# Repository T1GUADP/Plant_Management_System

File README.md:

# Plant_Management_System
This is a project created by: team 1; Real Time Embedded Programming; Glasgow University

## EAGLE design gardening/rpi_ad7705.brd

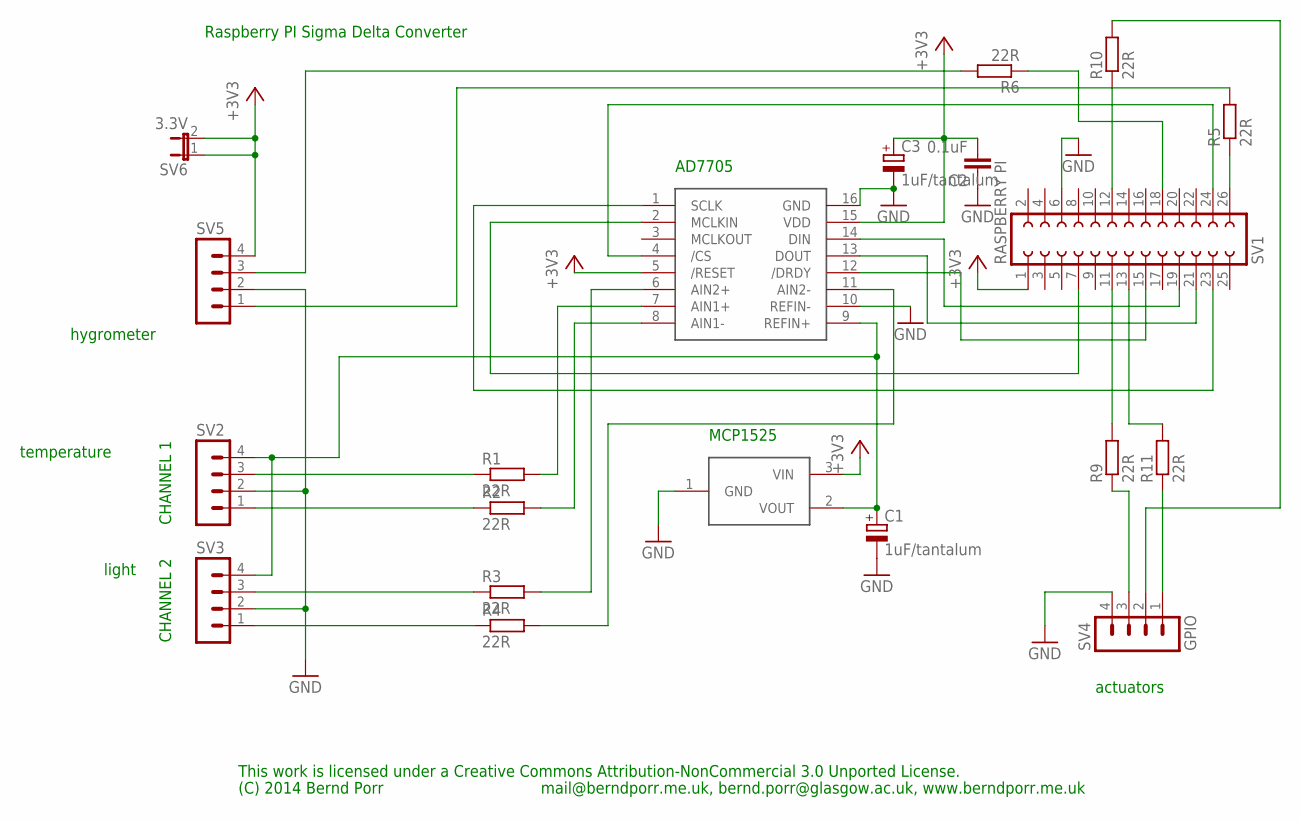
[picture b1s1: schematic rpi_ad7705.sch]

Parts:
C1, C3: 1uF/tantalum; TT2D7
C2: 0.1uF; C5B2.5
R1, R2, R3, R4, R5, R6, R9, R10, R11: 22R; 0207/10
SV1: RASPBERRY PI; FE13-2
SV2, SV3, SV5: MA04-1
SV4: GPIO; MA04-1
SV6: 3.3V; JP1
U$1: AD7705; DIP16
U$2: MCP1525; TO92

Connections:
+3V3: C2.2, C3.+, SV1.1, SV5.4, SV6.1, SV6.2, U$1.5 (/RESET), U$1.15 (VDD), U$2.3 (VIN)
GND: C1.-, C2.1, C3.-, SV1.6, SV2.2, SV3.2, SV4.4, SV5.2, U$1.10 (REFIN-), U$1.16 (GND), U$2.1 (GND)
unnamed: SV1.19, U$1.14 (DIN)
unnamed: SV1.23, U$1.1 (SCLK)
unnamed: SV1.7, U$1.2 (MCLKIN)
unnamed: SV1.24, U$1.4 (/CS)
unnamed: C1.+, SV2.4, SV3.4, U$1.9 (REFIN+), U$2.2 (VOUT)
unnamed: SV1.21, U$1.13 (DOUT)
unnamed: R2.2, U$1.8 (AIN1-)
unnamed: R1.2, U$1.7 (AIN1+)
unnamed: R3.2, U$1.6 (AIN2+)
unnamed: R4.2, U$1.11 (AIN2-)
unnamed: R1.1, SV2.3
unnamed: R2.1, SV2.1
unnamed: R3.1, SV3.3
unnamed: R4.1, SV3.1
unnamed: R9.2, SV1.11
unnamed: R10.1, SV1.12
unnamed: R11.2, SV1.13
unnamed: R9.1, SV4.3
unnamed: R11.1, SV4.1
unnamed: R10.2, SV4.2
unnamed: SV1.15, U$1.12 (/DRDY)
unnamed: R5.2, SV5.1
unnamed: R5.1, SV1.26
unnamed: R6.1, SV1.18
unnamed: R6.2, SV5.3

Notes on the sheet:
This work is licensed under a Creative Commons Attribution-NonCommercial 3.0 Unported License.
(C) 2014 Bernd Porr
mail@berndporr.me.uk, bernd.porr@glasgow.ac.uk, www.berndporr.me.uk
AD7705
MCP1525
CHANNEL 1
CHANNEL 2
Raspberry PI Sigma Delta Converter
hygrometer
temperature
light
actuators

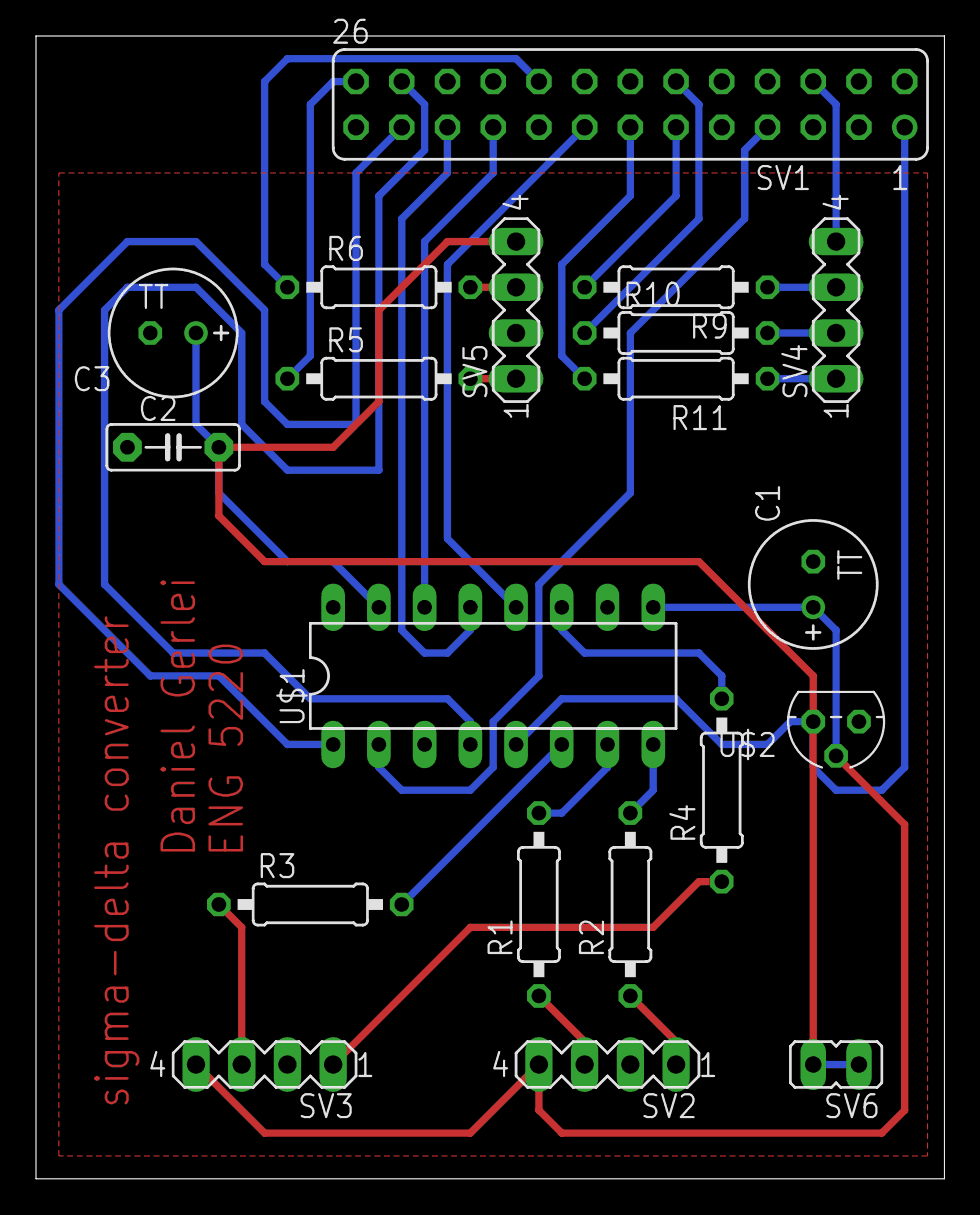
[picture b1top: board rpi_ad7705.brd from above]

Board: 2 copper layers, 50.5 x 63.5 mm, 20 parts (0 on the bottom side), 27 nets.

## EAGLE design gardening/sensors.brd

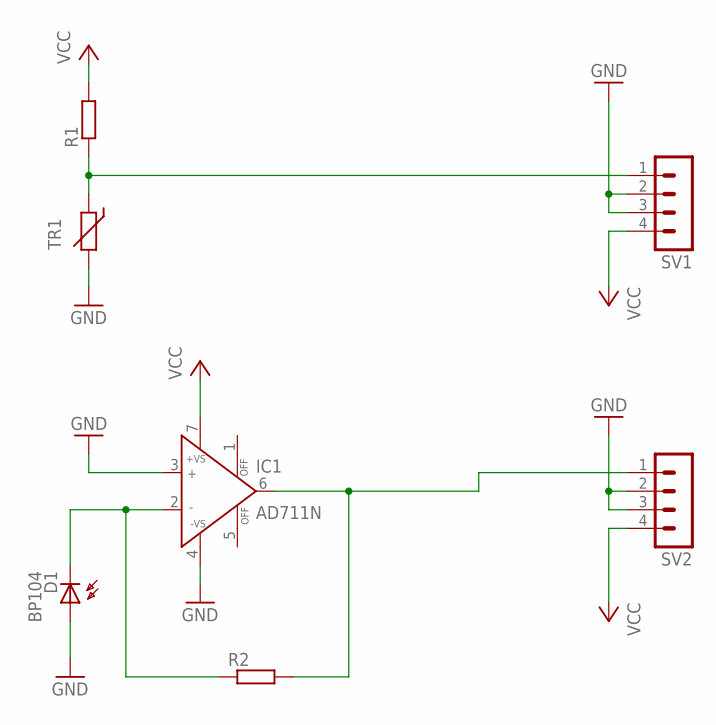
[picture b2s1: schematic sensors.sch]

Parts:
D1: BP104
IC1: AD711N; DIL08
R1: R-EU_0204/7; 0204/7
R2: R0204/7; 0204/7
SV1, SV2: MA04-1
TR1: THERMISTOR_; TO92

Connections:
GND: D1.A, IC1.3 (IN+), IC1.4 (-VS), SV1.2, SV1.3, SV2.2, SV2.3, TR1.2
unnamed: R1.1, SV1.1, TR1.1
unnamed: D1.K (C), IC1.2 (IN-), R2.1
unnamed: IC1.6 (OUT), R2.2, SV2.1
VCC: IC1.7 (+VS), R1.2, SV1.4, SV2.4

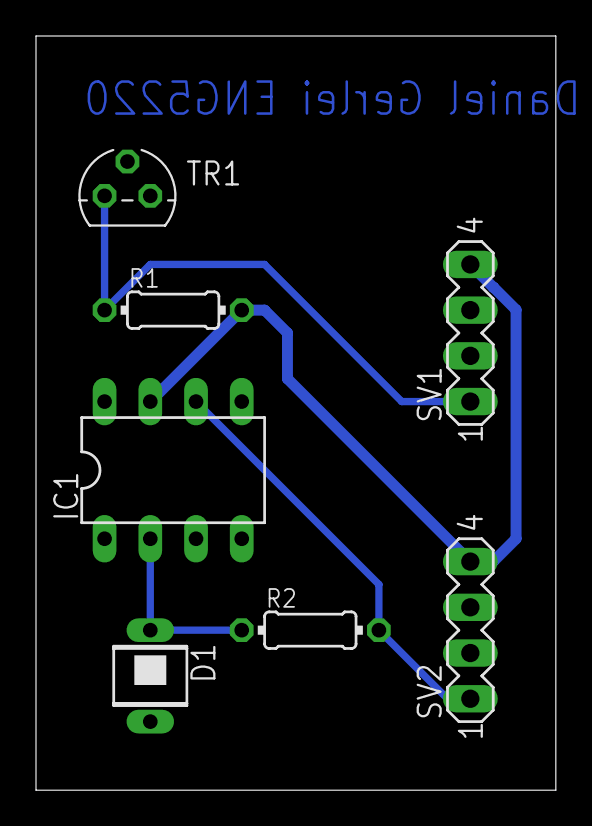
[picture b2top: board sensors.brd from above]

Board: 2 copper layers, 28.9 x 41.9 mm, 7 parts (0 on the bottom side), 5 nets.

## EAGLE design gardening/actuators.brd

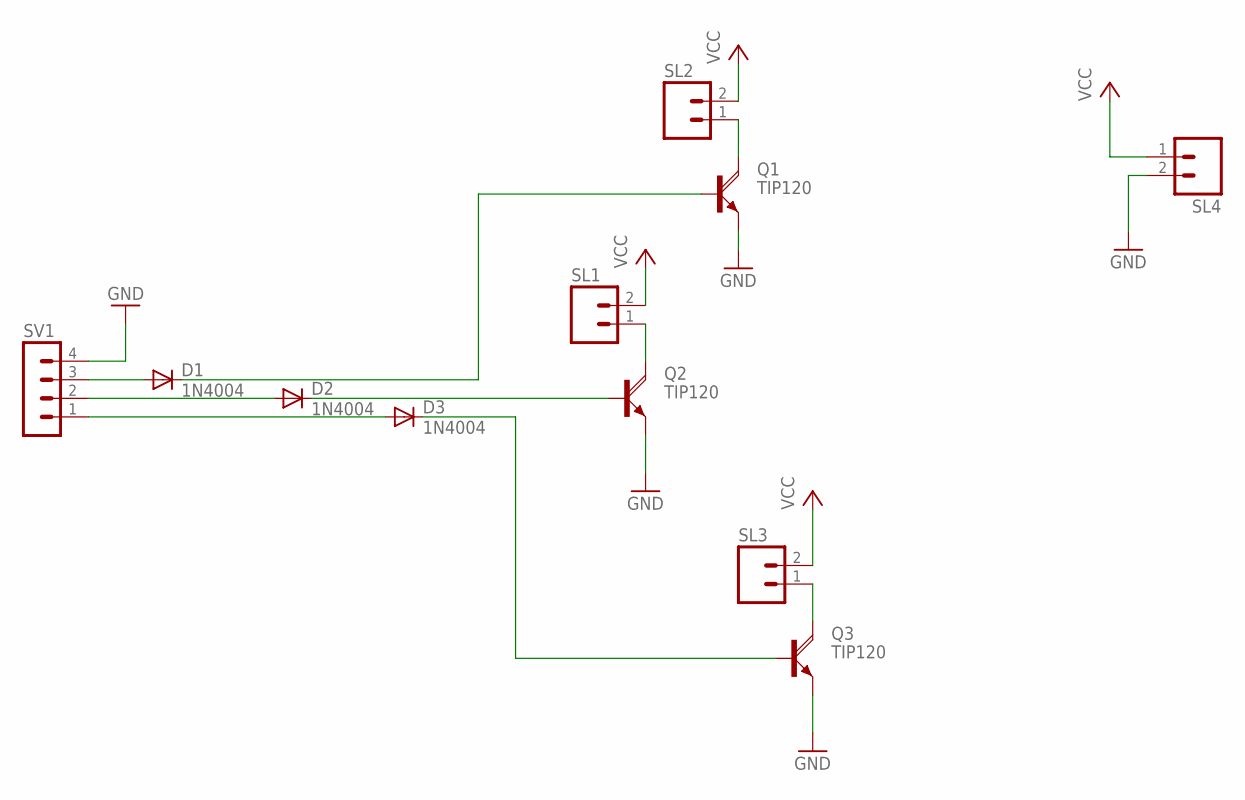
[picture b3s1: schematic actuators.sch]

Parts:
D1, D2, D3: 1N4004; DO41-10
Q1, Q2, Q3: TIP120; TO220AH
SL1, SL2, SL3, SL4: MA02; 02PA
SV1: MA04-1

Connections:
GND: Q1.E, Q2.E, Q3.E, SL4.2, SV1.4
unnamed: D1.C, Q1.B
unnamed: D1.A, SV1.3
unnamed: D2.A, SV1.2
unnamed: Q1.C, SL2.1
unnamed: Q2.C, SL1.1
unnamed: Q3.C, SL3.1
unnamed: D2.C, Q2.B
unnamed: D3.A, SV1.1
unnamed: D3.C, Q3.B
VCC: SL1.2, SL2.2, SL3.2, SL4.1

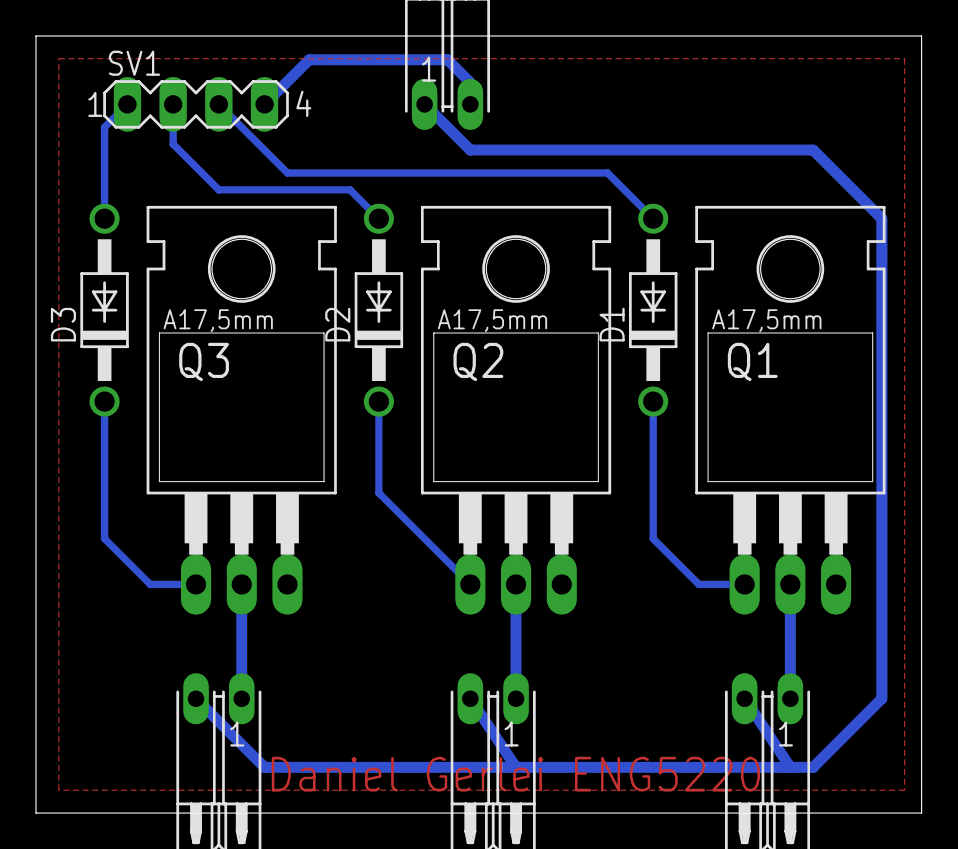
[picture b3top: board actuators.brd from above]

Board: 2 copper layers, 49.2 x 43.2 mm, 11 parts (0 on the bottom side), 11 nets.

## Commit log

2017-03-27 Add files via upload
    Please note that this version is a derivative of Berd Porr's "qwt-example" (https://github.com/berndporr/qwt-example.git)
2017-04-11 Add files via upload
    These files are the backups created when no internet connection was available.
2017-04-15 Add files via upload
    Pictures for wiki of hardware
2017-04-16 Add files via upload
    Changelog.
    0.0.1
    date: -Added ModeButton //Toggles current mode (Auto/Manual) (non-functional)
    20.3.16 -Added ModeTextLabel1 //"CurrentMode:" (non-functional)
    -Added ModeTextLabel2 //displays current mode (Auto/Manual) (non-functional)
    -Added ExitButton //Exits application (non-functional)
2017-04-16 Add files via upload
    Final version 0.0.8
